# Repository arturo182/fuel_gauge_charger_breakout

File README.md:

# Fuel Gauge and Battery Charger Breakout

This is a breakout board for the BQ27421-G1 fuel gauge and the MCP73871 battery charger.

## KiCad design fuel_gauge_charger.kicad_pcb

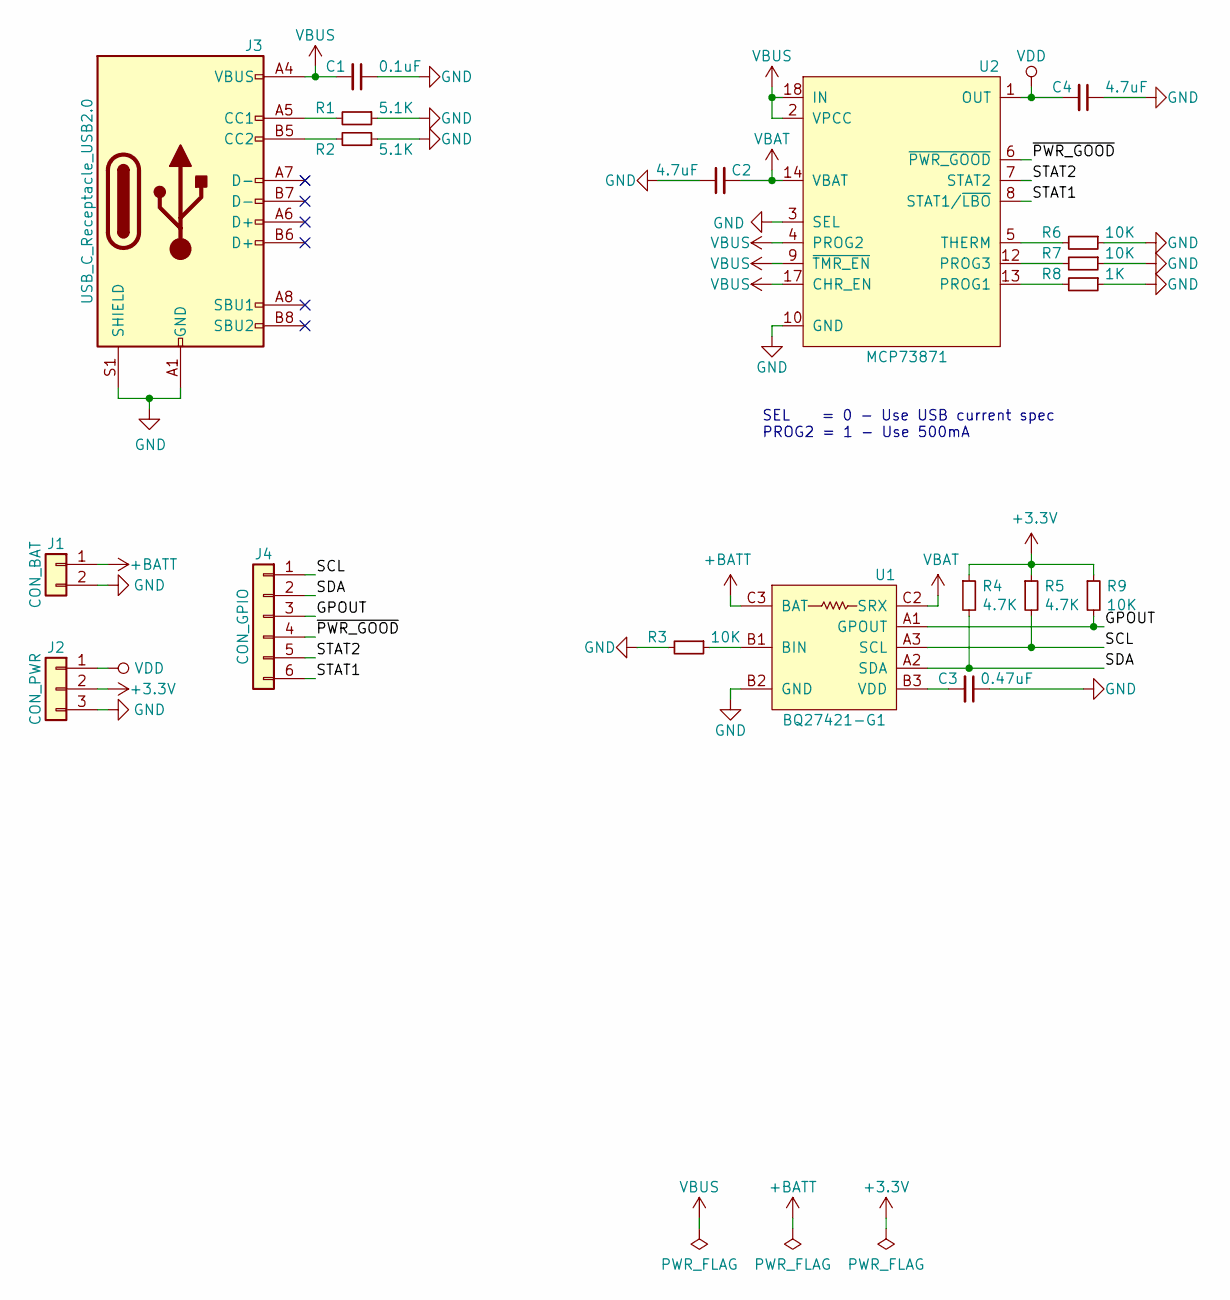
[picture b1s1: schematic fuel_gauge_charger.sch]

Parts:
C1: 0.1uF; C_0603_1608Metric
C2, C4: 4.7uF; C_0603_1608Metric
C3: 0.47uF; C_0603_1608Metric
J1: CON_BAT; PinHeader_1x02_P2.54mm_Vertical
J2: CON_PWR; PinHeader_1x03_P2.54mm_Vertical
J3: USB_C_Receptacle_USB2.0; USB_C_Receptacle_GT-USB-7010
J4: CON_GPIO; PinHeader_1x06_P2.54mm_Vertical
R1, R2: 5.1K; R_0402_1005Metric
R3, R6, R7, R9: 10K; R_0402_1005Metric
R4, R5: 4.7K; R_0402_1005Metric
R8: 1K; R_0402_1005Metric
U1: BQ27421-G1; BGA-9_1.6x1.6mm_Layout3x3_P0.5mm
U2: MCP73871; QFN-20_EP_4x4_Pitch0.5mm

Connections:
+3V3: J2.2, R4.1, R5.1, R9.1
+BATT: J1.1, U1.C3 (BAT)
/GPOUT: J4.3, R9.2, U1.A1 (GPOUT)
/SCL: J4.1, R5.2, U1.A3 (SCL)
/SDA: J4.2, R4.2, U1.A2 (SDA)
/STAT1: J4.6, U2.8 (STAT1/~LBO~)
/STAT2: J4.5, U2.7 (STAT2)
/~PWR_GOOD~: J4.4, U2.6 (~PWR_GOOD~)
GND: C1.1, C2.1, C3.1, C4.1, J1.2, J2.3, J3.A1 (GND), J3.A12 (GND), J3.B1 (GND), J3.B12 (GND), J3.S1 (SHIELD), R1.1, R2.1, R3.2, R6.1, R7.1, R8.1, U1.B2 (GND), U1.C1 (GND), U2.3 (SEL), U2.10 (GND), U2.11 (GND), U2.21 (GND)
unnamed: C3.2, U1.B3 (VDD)
unnamed: J3.A5 (CC1), R1.2
unnamed: J3.B5 (CC2), R2.2
unnamed: R3.1, U1.B1 (BIN)
unnamed: R6.2, U2.5 (THERM)
unnamed: R7.2, U2.12 (PROG3)
unnamed: R8.2, U2.13 (PROG1)
VBAT: C2.2, U1.C2 (SRX), U2.14 (VBAT), U2.15 (VBAT), U2.16 (VBAT)
VBUS: C1.2, J3.A4 (VBUS), J3.A9 (VBUS), J3.B4 (VBUS), J3.B9 (VBUS), U2.2 (VPCC), U2.4 (PROG2), U2.9 (~TMR_EN~), U2.17 (CHR_EN), U2.18 (IN), U2.19 (IN)
VDD: C4.2, J2.1, U2.1 (OUT), U2.20 (OUT)

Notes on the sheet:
SEL = 0 - Use USB current spec PROG2 = 1 - Use 500mA

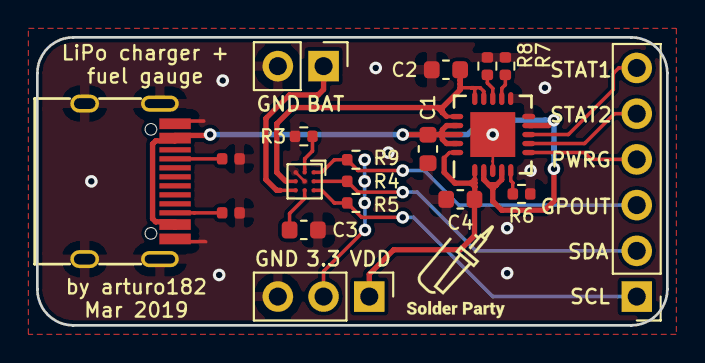
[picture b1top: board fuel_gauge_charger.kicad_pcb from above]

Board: 2 copper layers, 35.0 x 16.0 mm, 19 parts (0 on the bottom side), 19 nets.

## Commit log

2019-03-07 Initial import
2019-05-01 Change to submodules, add readme
2019-05-11 Added images
